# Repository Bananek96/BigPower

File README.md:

# Technologie Elektroniki Mocy I Wysokich Częstotliwości

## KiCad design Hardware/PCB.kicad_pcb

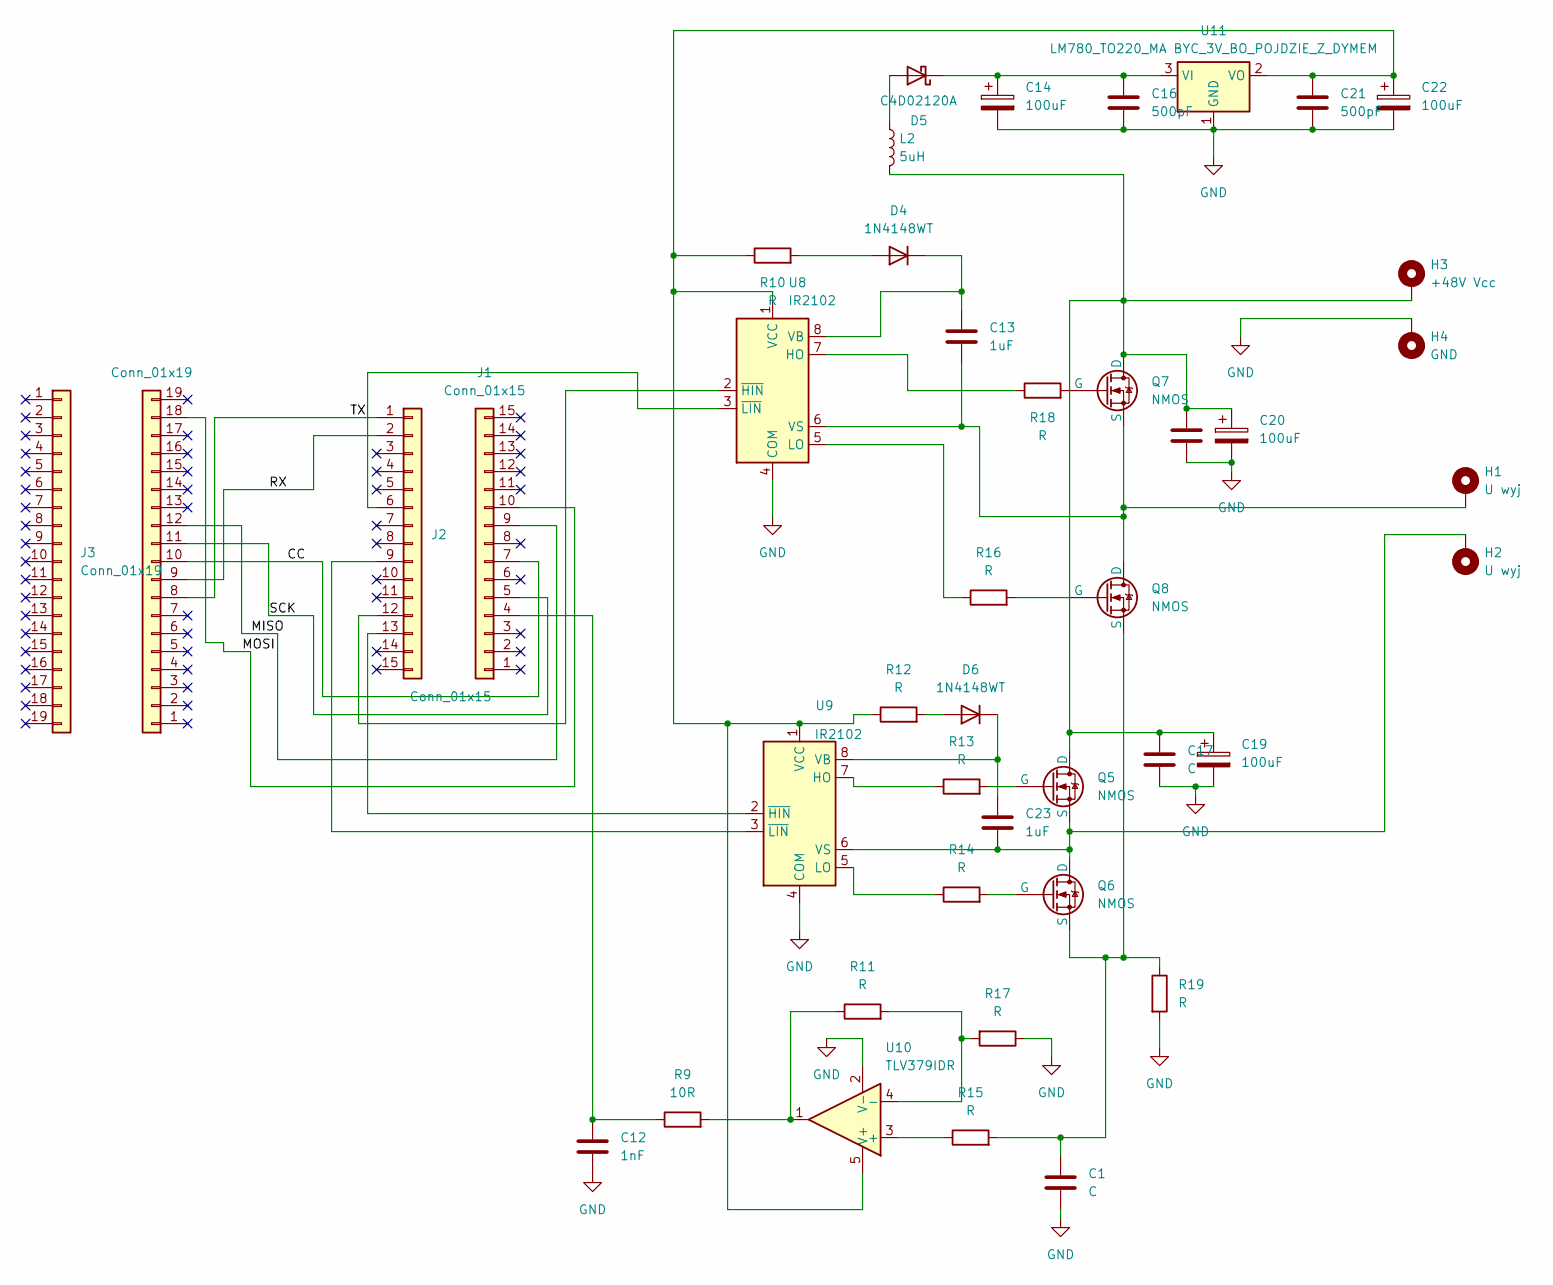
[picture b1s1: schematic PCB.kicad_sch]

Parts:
C1, C17, C18: C; C_1206_3216Metric
C12: 1nF; C_1206_3216Metric
C13, C23: 1uF; C_1206_3216Metric
C14, C19, C20, C22: 100uF; CP_Elec_10x10
C16, C21: 500pF; C_1206_3216Metric
D4, D6: 1N4148WT; D_MiniMELF
D5: C4D02120A; TO-220-2_Vertical
H1, H2: U wyj; MountingHole_3.2mm_M3_DIN965_Pad
H3: +48V Vcc; MountingHole_3.2mm_M3_DIN965_Pad
H4: GND; MountingHole_3.2mm_M3_DIN965_Pad
J1, J2: Conn_01x15; PinHeader_1x15_P2.54mm_Vertical
J3, J4: Conn_01x19; PinHeader_1x19_P2.54mm_Vertical
L2: 5uH; L_6.3x6.3_H3
Q5, Q6, Q7, Q8: NMOS; TO-220-3_Horizontal_TabUp
R9: 10R; R_1210_3225Metric
R10, R11, R12, R13, R14, R15, R16, R17, R18, R19: R; R_1210_3225Metric
U8, U9: IR2102; SOIC-8-1EP_3.9x4.9mm_P1.27mm_EP2.29x3mm
U10: TLV379IDR; SOT-23-5
U11: LM780_TO220_MA BYC_3V_BO_POJDZIE_Z_DYMEM; TO-220-3_Horizontal_TabUp

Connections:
/CC: J1.7, J4.10
/MISO: J1.9, J4.12
/MOSI: J1.10, J4.18
/RX: J2.2, J4.9
/SCK: J1.5, J4.11
/TX: J2.1, J4.8
GND: C1.2, C12.2, C14.2, C16.2, C17.2, C18.2, C19.2, C20.2, C21.2, C22.2, H4.1, R17.1, R19.2, U8.4 (COM), U9.4 (COM), U10.2 (V-), U11.1 (GND)
unnamed: D4.2 (A), R10.2
unnamed: C13.1, D4.1 (K), U8.8 (VB)
unnamed: D5.2 (A), L2.1
unnamed: C14.1, C16.1, D5.1 (K), U11.3 (VI)
unnamed: D6.2 (A), R12.2
unnamed: C23.1, D6.1 (K), U9.8 (VB)
unnamed: C12.1, J1.4, R9.1
unnamed: J2.6, U8.3 (~LIN)
unnamed: J2.9, U9.3 (~LIN)
unnamed: J2.12, U8.2 (~HIN)
unnamed: J2.13, U9.2 (~HIN)
unnamed: C17.1, C18.1, C19.1, C20.1, H3.1, L2.2, Q5.1 (D), Q7.1 (D)
unnamed: Q5.2 (G), R13.2
unnamed: C23.2, H2.1, Q5.3 (S), Q6.1 (D), U9.6 (VS)
unnamed: Q6.2 (G), R14.2
unnamed: C1.1, Q6.3 (S), Q8.3 (S), R15.2, R19.1
unnamed: Q7.2 (G), R18.2
unnamed: C13.2, H1.1, Q7.3 (S), Q8.1 (D), U8.6 (VS)
unnamed: Q8.2 (G), R16.2
unnamed: R9.2, R11.1, U10.1
unnamed: R18.1, U8.7 (HO)
unnamed: R16.1, U8.5 (LO)
unnamed: R13.1, U9.7 (HO)
unnamed: R14.1, U9.5 (LO)
unnamed: R15.1, U10.3 (+)
unnamed: R11.2, R17.2, U10.4 (-)
unnamed: C21.1, C22.1, R10.1, R12.1, U8.1 (VCC), U9.1 (VCC), U10.5 (V+), U11.2 (VO)

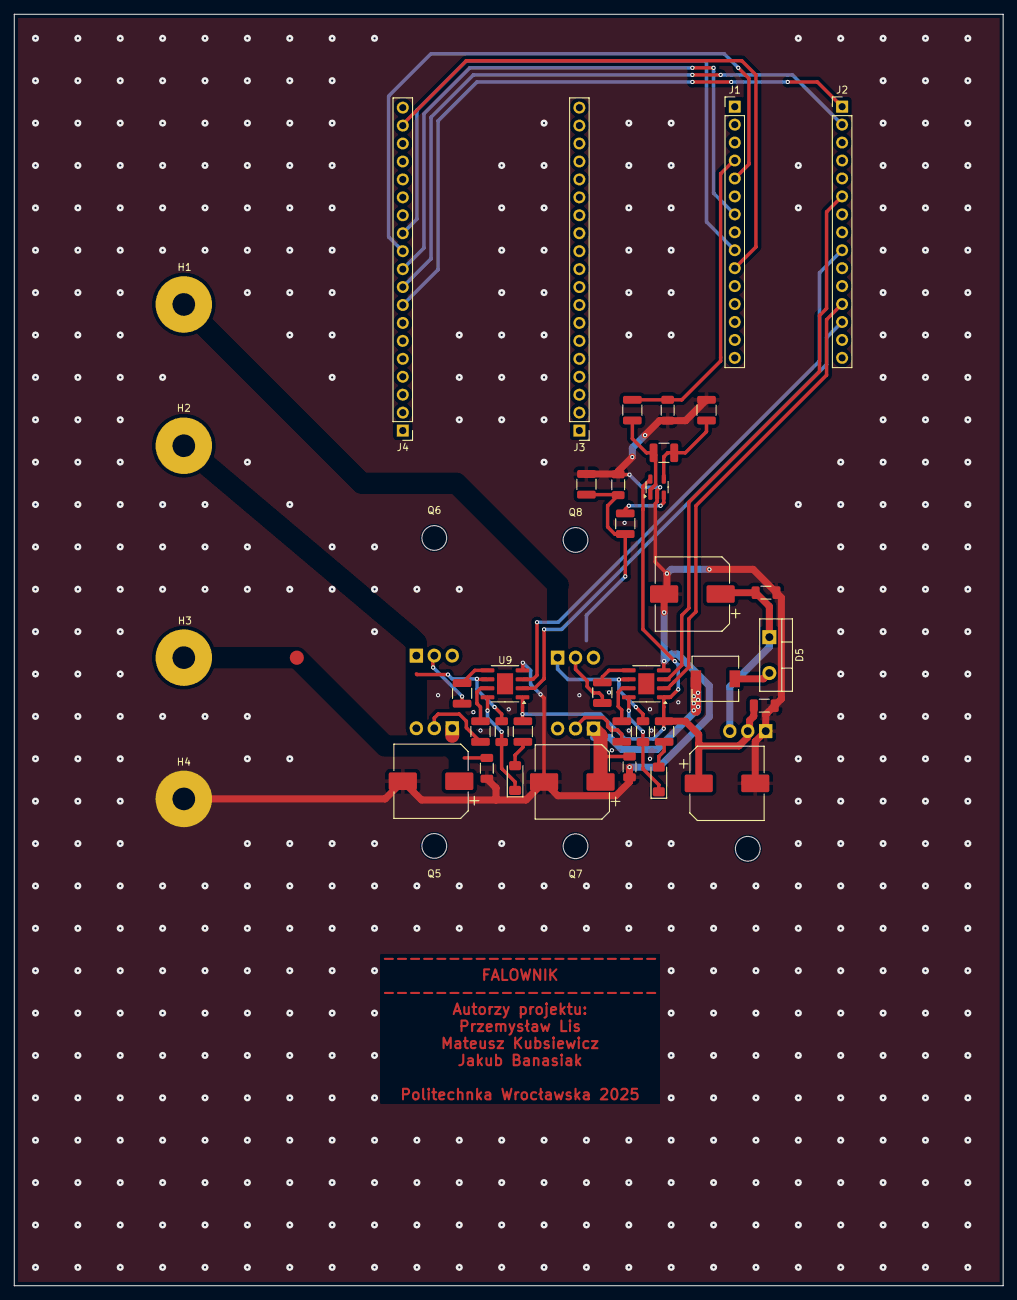
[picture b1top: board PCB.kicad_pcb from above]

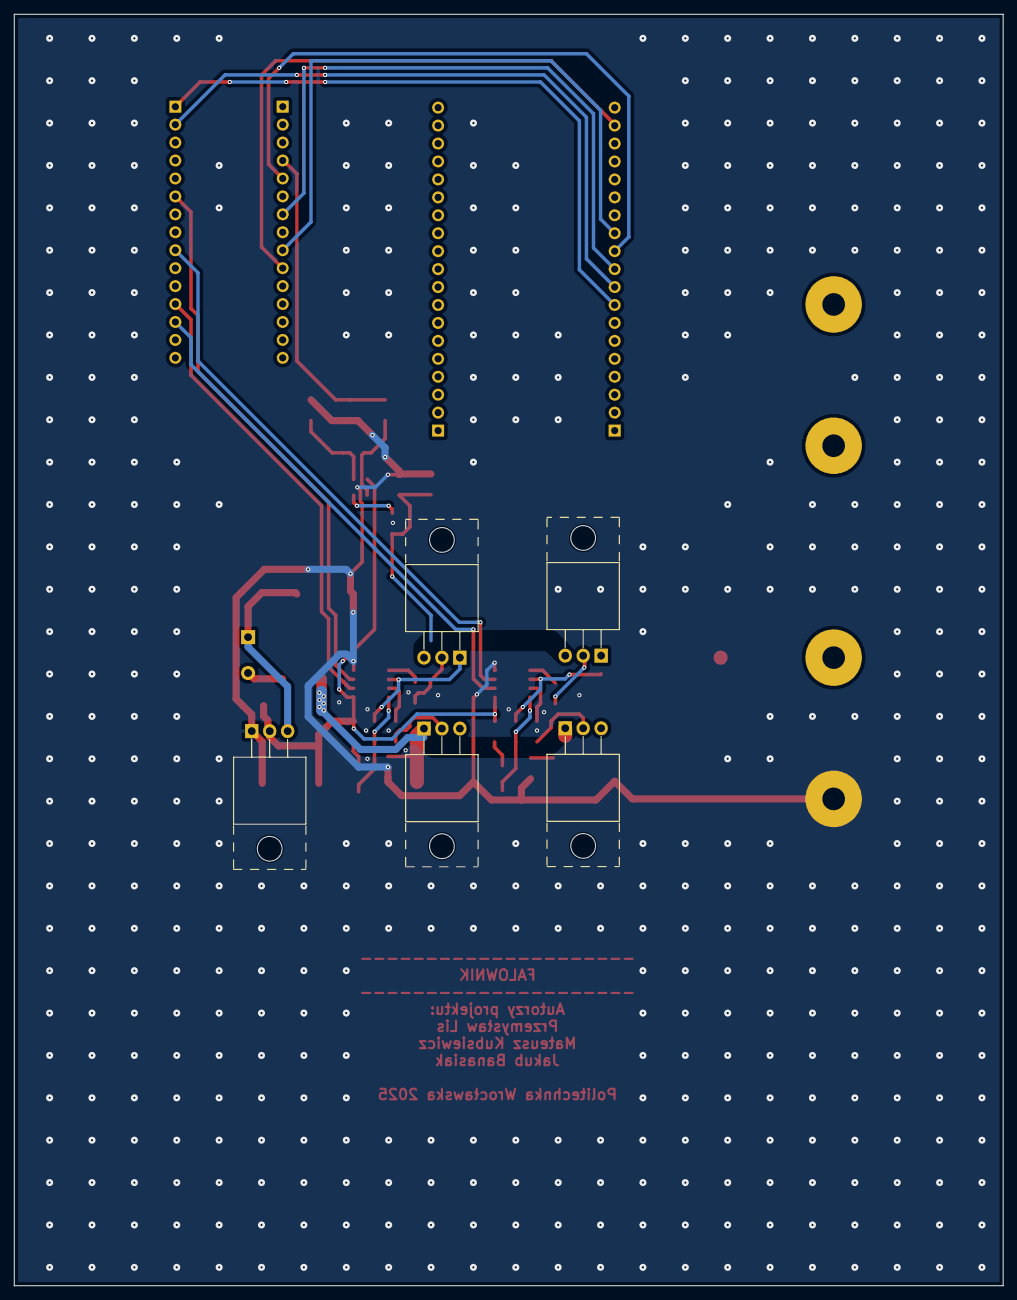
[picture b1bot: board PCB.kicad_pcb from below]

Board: 2 copper layers, 140.0 x 180.0 mm, 43 parts (5 on the bottom side), 34 nets.

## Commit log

2025-04-02 First_steps
2025-04-04 Dodanie czesci mocowej w hardware
2025-04-09 test
2025-04-09 Schemat-update
2025-04-09 Added opamp
2025-04-09 Added stm32 project and connect opamp
2025-04-09 notes
2025-04-16 KICAD UPDATE
    Zmodyfikowałem schemat, finalna wersja
2025-04-16 dodanie footprintów
2025-04-16 Jakies zmiany
2025-04-17 Złącza zasilające
2025-04-23 Added PCB
2025-04-23 New update
2025-04-28 1
    1
2025-04-28 Repair some bugs
2025-04-28 added footprints
2025-04-29 1
    Płytka gotowa do trasowania ścieżek
2025-04-30 Cos tam sie zmenia
2025-04-30 1
    sortowanie kluczy ok
2025-04-30 1
    ogarnieta plytka, elementy rozmieszczone, zostalo zrobic sciezki
2025-05-05 05.05.25
    Mamy bledy, chujowo jest
2025-05-09 09.05.25
    Robimy płytkę dwustronną, jest problem z połączeniem w obrębie tranzystorów
2025-05-19 1
    Część finalna połączona, trzeba zrobić pole GND i zrobić przelotki GND
2025-05-27 1
    trzeba zrobić pole gnd z przelotkami, dorobić odpowiedni rozmiar płytki i otwory na śruby oraz zdjąć maskę na ścieżkach prądowych
2025-05-28 1
    trzeba zrobić pole gnd, przelotki gnd i ustawić wymiary pcb
2025-05-28 1
    trzeba zrobić siatkę przelotek i usunąć maskę z torów prądowych
2025-06-10 Save before using via-stiching script
2025-06-10 Commit gitignore for KiCad
    From this GitHub Gist: https://gist.github.com/cowboy/71a35998640eb5a6c50680c979b35187
2025-06-10 Move gitignore to project dir
2025-06-10 Run via stitching
    Vias 1mm size/0.3mm, spacing 6x6mm, clearance 3mm
2025-06-10 finał
    finał
2025-06-10 final
    final
2025-06-11 webapp
2025-06-14 puyhon + esp32
2025-06-18 Pliki symulacji
    Pliki symulacji
